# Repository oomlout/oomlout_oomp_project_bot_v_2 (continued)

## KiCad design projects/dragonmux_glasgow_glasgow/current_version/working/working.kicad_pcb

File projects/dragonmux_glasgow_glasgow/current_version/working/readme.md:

# glasgow
 
## summary 
* id: dragonmux_glasgow_glasgow
* user: dragonmux
* name: glasgow
* board: glasgow
* repo: https://github.com/dragonmux/glasgow
* src_file_repo_kicad_pcb: hardware/boards/glasgow.kicad_pcb
* src_file_repo_kicad_pcb_link: https://github.com/dragonmux/glasgow/tree/main/hardware/boards/glasgow.kicad_pcb

* src_file_repo_sch: hardware/boards/glasgow.sch
* src_file_repo_sch_link: https://github.com/dragonmux/glasgow/tree/main/hardware/boards/glasgow.sch
* full details link: https://github.com/oomlout/oomlout_oomp_project_bot_v_2/tree/main/projects/dragonmux_glasgow_glasgow/current_version/working

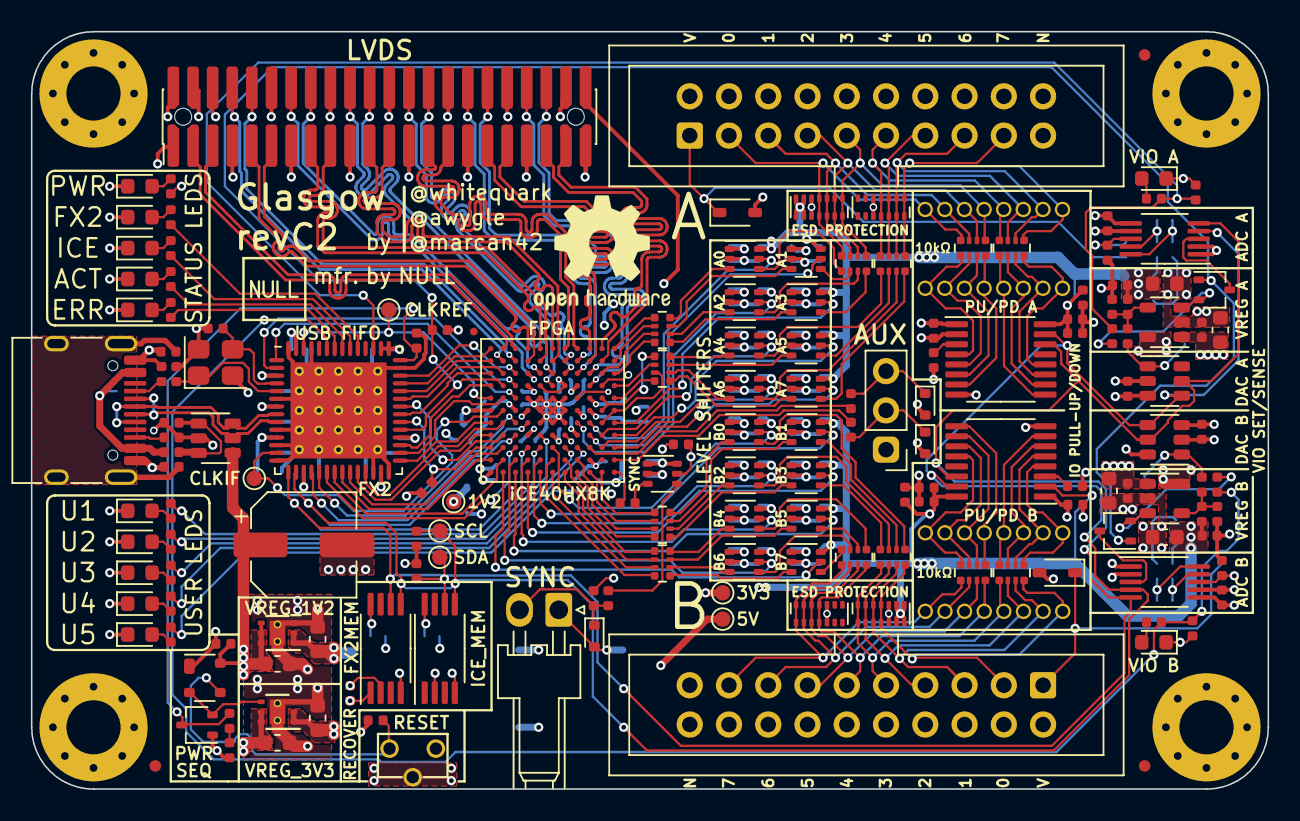
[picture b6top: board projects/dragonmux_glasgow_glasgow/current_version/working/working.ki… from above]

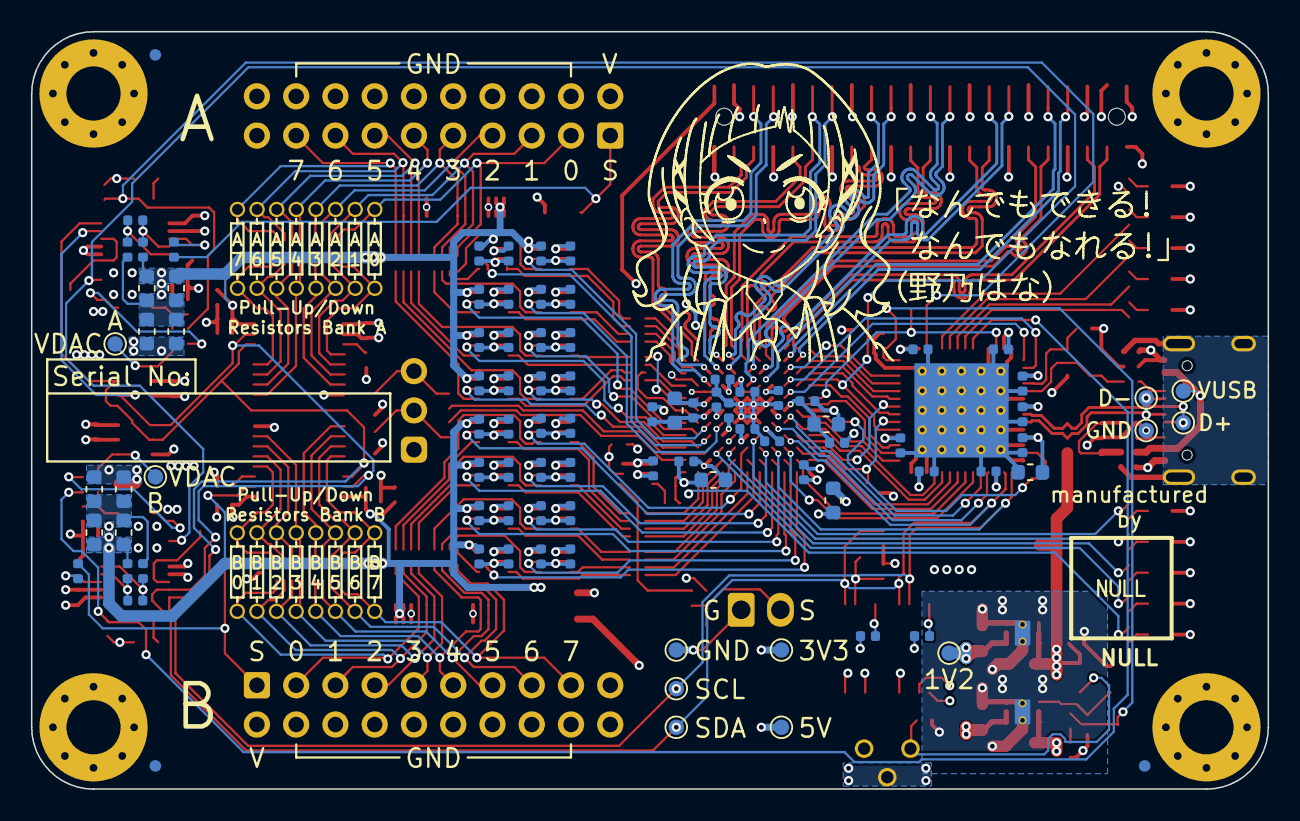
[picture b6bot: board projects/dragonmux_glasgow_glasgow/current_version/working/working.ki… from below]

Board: 4 copper layers, 80.0 x 49.0 mm, 264 parts (93 on the bottom side), 226 nets.

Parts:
C1, C14, C19, C26, C27, C28, C31, C53, C76, C80, C82, C83, C86: 4u7; C_0603_1608Metric
C2, C3, C4, C5, C6, C7, C8, C9, C10, C13, C15, C16, C17, C18, C20, C21, C22, C23, C24, C25, C29, C30, C32, C33, C34, C35, C36, C37, C38, C39, C40, C41, C42, C43, C44, C45, C46, C47, C48, C49, C50, C51, C52, C54, C55, C56, C57, C58, C59, C60, C61, C62, C63, C64, C65, C66, C67, C68, C69, C70, C71, C72, C73, C74, C75, C77, C78, C79, C81, C84, C85, C88, C89: u1; C_0402_1005Metric
C11, C12: 9p; C_0402_1005Metric
C87: 150u; CP_Elec_6.3x5.9
C90, C91: DNP; C_0402_1005Metric_DNP
D1, D2, D3, D14, D15: GRN; LED_0603_1608Metric
D4: YEL; LED_0603_1608Metric
D5: RED; LED_0603_1608Metric
D6, D10: BLU; LED_0603_1608Metric
D7, D9: PNK; LED_0603_1608Metric
D8: WHT; LED_0603_1608Metric
D11, D12, D13: ESD5Z5.0T1G; D_SOD-523
D16, D17: CDSOD323-T36S; D_SOD-323
D18, D19: BAT54CW; SOT-323_SC-70
D20, D21, D22, D23: SP3012-06UTG; UDFN-14_3.5x1.35mm_P0.5mm
D24: BAT54AW; SOT-323_SC-70
FB1: 600R, 0.5A; L_0402_1005Metric
FID1, FID2, FID3, FID4, FID5, FID6: Fiducial_0.75mm_Mask1.5mm
FID8: Fiducial_0.5mm_Dia_1mm_Outer
J1: USB_C_USB2.0; USB_C_Receptacle_HRO_TYPE-C-31-M-12
J2, J3: IDC-Header_2x10_P2.54mm; IDC-Header_2x10_P2.54mm_Vertical
J4: Conn_01x02; Molex_KK-254_1x02_P2.54mm_Horizontal
J5: PinHeader_2x22_P1.27mm; PinHeader_2x22_P1.27mm_Vertical__SMD
J6, J7, J8, J9: Conn_01x08; PinSocket_1x08_P1.27mm_Vertical_DNP
J10: AUX; PinHeader_1x03_P2.54mm_Vertical
MK1, MK2, MK3, MK4: Mounting_Hole_PAD; MountingHole_3.5mm_Pad_Via_CrtYd
NONO_HANA: MECHOKKU; nono_hana_lines
R1, R2, R10, R15, R41, R42, R57, R58: 2k2; R_0402_1005Metric
R3, R4, R5, R9, R17: 100k; R_0402_1005Metric
R6, R8, R50, R51: DNP; R_0603_1608Metric_DNP
R7, R56: 0R33; R_0603_1608Metric
R11, R23: 4k7; R_0402_1005Metric
R12, R13, R14, R46, R47: 20k; R_0402_1005Metric
R16, R18, R19, R20, R22, R26, R36, R37, R44, R55: 10k; R_0402_1005Metric
R21: 6k8; R_0402_1005Metric
R24, R25, R30, R54, R59, R60: 4R7; R_0402_1005Metric
R27, R33: 49k9; R_0402_1005Metric
R28, R34: 59k; R_0402_1005Metric
R29, R35: 24k3; R_0402_1005Metric
R31, R32: 100R; R_0402_1005Metric
R38, R39, R43, R45: 47R; R_0402_1005Metric
R40: DNP; R_0402_1005Metric_DNP
R48, R49: 0R15; R_0603_1608Metric
R52, R53: 5k1; R_0402_1005Metric
RN1, RN2, RN3, RN4, RN7, RN8, RN9, RN10: 33R; R_Array_Convex_4x0402
RN5, RN6, RN11, RN12: 10k; R_Array_Convex_4x0402
SW1: RST; SW_Tactile_SPST_Angled_TC-1109DE
TP1, TP8: 5V; TestPoint_Pad_D1.0mm
TP2, TP17: 1V2; TestPoint_Pad_D1.0mm
TP3, TP7, TP9: 3V3; TestPoint_Pad_D1.0mm
TP4, TP10: SDA; TestPoint_Pad_D1.0mm
TP5, TP11: SCL; TestPoint_Pad_D1.0mm
TP6: CLKREF; TestPoint_Pad_D1.0mm
TP12: GND; TestPoint_Pad_D1.0mm
TP13: VBUS; TestPoint_Pad_D1.0mm
TP14: USBGND; TestPoint_Pad_D1.0mm
TP15: USBDP; TestPoint_Pad_D1.0mm
TP16: USBDM; TestPoint_Pad_D1.0mm
TP18, TP19: VDAC; TestPoint_Pad_D1.0mm
U1: CY7C68013A-56LTX; Cypress_QFN-56-1EP_8x8mm_P0.5mm_EP6.22x6.22mm_ThermalVias
U2: CAT24M01X; TSSOP-8_4.4x3mm_P0.65mm
U3: BL24C256A-SFRC; TSSOP-8_4.4x3mm_P0.65mm
U4, U6, U9, U10, U11, U16, U17, U18, U22, U23, U24, U25, U26, U27, U28, U29, U32: SN74LVC1T45DCKR; SOT-363_SC-70-6
U5, U19: PCA6408APW; TSSOP-16_4.4x5mm_P0.65mm
U7: APX811-40UG-7; SOT-143
U8: TLV75533PDRVR; DFN-6-1EP_2x2mm_P0.65mm_EP1x1.6mm_ThermalVias
U12, U21: INA233; VSSOP-10_3x3mm_P0.5mm
U13, U20: DAC081C081CIMK; SOT-23-6
U14, U31: TPS73101DBV; SOT-23-5
U15: TPD3S014; SOT-23-6
U30: ICE40HX8K-BG121; BGA-121_9.0x9.0mm_Layout11x11_P0.8mm_Ball0.4mm_Pad0.35mm_NS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
U36: TLV73312PQDRVR; DFN-6-1EP_2x2mm_P0.65mm_EP1x1.6mm_ThermalVias
Y1: 24M; Crystal_SMD_3225-4Pin_3.2x2.5mm

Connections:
+1V2: C14.1, C18.1, C24.1, C25.1, C27.1, C77.1, R31.2, R32.2, TP2.1, TP17.1, U30.D4, U30.D8, U30.H4, U30.H8, U36.1, U36.2
+3V3: C1.1, C2.1, C3.1, C4.1, C5.1, C6.1, C7.1, C9.1, C10.1, C15.1, C17.1, C19.1, C20.1, C21.1, C22.1, C23.1, C28.1, C30.1, C32.1, C34.1, C35.1, C36.1, C37.1, C42.1, C43.1, C47.1, C48.1, C55.1, C56.1, C60.1, C61.1, C62.1, C63.1, C68.1, C69.1, C70.1, C71.1, C81.1, C84.1, C85.1, D24.1, J5.2, R1.2, R2.2, R4.1, R12.1, R17.2, R36.2, R37.2, R40.2, R44.2, TP3.1, TP9.1, U1.3, U1.7, U1.11, U1.17, U1.27, U1.32, U1.43, U1.44, U1.55, U2.2, U2.8, U3.1, U3.8, U4.1, U5.1, U6.1, U8.1, U8.2, U9.1, U10.1, U11.1, U12.2, U12.6, U13.2, U16.1, U17.1, U18.1, U19.1, U20.2, U21.6, U22.1, U23.1, U24.1, U25.1, U26.1, U27.1, U28.1, U29.1, U30.C10, U30.D6, U30.F8, U30.H6, U30.L11, U32.1, U32.6
+5V: C16.1, C26.2, C31.1, C45.1, C59.1, C82.1, C86.2, C87.1, TP1.1, TP8.1, U7.4, U8.5, U8.6, U14.1, U15.4, U31.1, U36.4, U36.5, U36.6
/A0: U1.37, U30.K3
/A1: U1.38, U30.L2
/CC1: J1.A5, R53.2
/CC2: J1.B5, R52.2
/CLKIF: TP7.1, U1.13, U30.K6
/CLKREF: TP6.1, U1.54, U30.D5, U30.L5
/D0: U1.18, U30.H7
/D1: U1.19, U30.J7
/D2: U1.20, U30.J9
/D3: U1.21, U30.K10
/D4: U1.22, U30.L10
/D5: U1.23, U30.K9
/D6: U1.24, U30.L8
/D7: U1.25, U30.K7
/ENVA: R18.1, R47.1, R55.2, U1.45
/ENVB: R19.1, R26.2, R46.1, U1.51
/FLAGA: U1.29, U30.L7
/FLAGB: U1.30, U30.K5
/FLAGC: U1.31, U30.L4
/FLAGD: U1.40, U30.J3
/FPGA_DONE: U1.36, U30.K8
/GNDPLL0: C76.2, C78.2, U30.L6
/GNDPLL1: C79.2, C80.2, U30.C5
/IO_Banks/DA0: U4.5, U30.C7
/IO_Banks/DA1: U11.5, U30.C8
/IO_Banks/DA2: U6.5, U30.D7
/IO_Banks/DA3: U16.5, U30.A7
/IO_Banks/DA4: U9.5, U30.B8
/IO_Banks/DA5: U17.5, U30.A8
/IO_Banks/DA6: U10.5, U30.B9
/IO_Banks/DA7: U18.5, U30.A9
/IO_Banks/DB0: U22.5, U30.F9
/IO_Banks/DB1: U26.5, U30.G11
/IO_Banks/DB2: U23.5, U30.G10
/IO_Banks/DB3: U27.5, U30.H11
/IO_Banks/DB4: U24.5, U30.H10
/IO_Banks/DB5: U28.5, U30.J11
/IO_Banks/DB6: U25.5, U30.J10
/IO_Banks/DB7: U29.5, U30.K11
/IO_Banks/IO_Buffer_A/ISNS_H: R8.2, R30.1, R49.1, R51.1, R56.2
/IO_Banks/IO_Buffer_A/P0: J9.1, RN11.5, U19.4
/IO_Banks/IO_Buffer_A/P1: J9.2, RN11.6, U19.5
/IO_Banks/IO_Buffer_A/P2: J9.3, RN11.7, U19.6
/IO_Banks/IO_Buffer_A/P3: J9.4, RN11.8, U19.7
/IO_Banks/IO_Buffer_A/P4: J9.5, RN12.5, U19.9
/IO_Banks/IO_Buffer_A/P5: J9.6, RN12.6, U19.10
/IO_Banks/IO_Buffer_A/P6: J9.7, RN12.7, U19.11
/IO_Banks/IO_Buffer_A/P7: J9.8, RN12.8, U19.12
/IO_Banks/IO_Buffer_A/VDAC: R33.1, TP19.1, U20.1
/IO_Banks/IO_Buffer_A/VFB: R33.2, R34.1, R35.2, U31.4
/IO_Banks/IO_Buffer_A/VIO_EN: D19.2, R55.1, U31.3
/IO_Banks/IO_Buffer_A/VSENSE: D17.1, J2.1, R60.2
/IO_Banks/IO_Buffer_A/X0: RN7.8, U4.3
/IO_Banks/IO_Buffer_A/Y0: RN9.1, U4.4
/IO_Banks/IO_Buffer_A/Y1: RN9.2, U11.4
/IO_Banks/IO_Buffer_A/Y2: RN9.3, U6.4
/IO_Banks/IO_Buffer_A/Y3: RN9.4, U16.4
/IO_Banks/IO_Buffer_A/Y4: RN10.1, U9.4
/IO_Banks/IO_Buffer_A/Y5: RN10.2, U17.4
/IO_Banks/IO_Buffer_A/Y6: RN10.3, U10.4
/IO_Banks/IO_Buffer_A/Y7: RN10.4, U18.4
/IO_Banks/IO_Buffer_A/Z0: D22.4, D22.11, J2.3, J8.1, RN9.8, RN11.4
/IO_Banks/IO_Buffer_A/Z1: D22.3, D22.12, J2.5, J8.2, RN9.7, RN11.3
/IO_Banks/IO_Buffer_A/Z2: D22.2, D22.13, J2.7, J8.3, RN9.6, RN11.2
/IO_Banks/IO_Buffer_A/Z3: D22.1, D22.14, J2.9, J8.4, RN9.5, RN11.1
/IO_Banks/IO_Buffer_A/Z4: D23.4, D23.11, J2.11, J8.5, RN10.8, RN12.4
/IO_Banks/IO_Buffer_A/Z5: D23.3, D23.12, J2.13, J8.6, RN10.7, RN12.3
/IO_Banks/IO_Buffer_A/Z6: D23.2, D23.13, J2.15, J8.7, RN10.6, RN12.2
/IO_Banks/IO_Buffer_A/Z7: D23.1, D23.14, J2.17, J8.8, RN10.5, RN12.1
/IO_Banks/IO_Buffer_B/ISNS_H: R6.2, R7.2, R24.1, R48.1, R50.1
/IO_Banks/IO_Buffer_B/P0: J7.1, RN5.5, U5.4
/IO_Banks/IO_Buffer_B/P1: J7.2, RN5.6, U5.5
/IO_Banks/IO_Buffer_B/P2: J7.3, RN5.7, U5.6
/IO_Banks/IO_Buffer_B/P3: J7.4, RN5.8, U5.7
/IO_Banks/IO_Buffer_B/P4: J7.5, RN6.5, U5.9
/IO_Banks/IO_Buffer_B/P5: J7.6, RN6.6, U5.10
/IO_Banks/IO_Buffer_B/P6: J7.7, RN6.7, U5.11
/IO_Banks/IO_Buffer_B/P7: J7.8, RN6.8, U5.12
/IO_Banks/IO_Buffer_B/VDAC: R27.1, TP18.1, U13.1
/IO_Banks/IO_Buffer_B/VFB: R27.2, R28.1, R29.2, U14.4
/IO_Banks/IO_Buffer_B/VIO_EN: D18.2, R26.1, U14.3
/IO_Banks/IO_Buffer_B/VSENSE: D16.1, J3.1, R59.2
/IO_Banks/IO_Buffer_B/X0: RN1.8, U22.3
/IO_Banks/IO_Buffer_B/Y0: RN3.1, U22.4
/IO_Banks/IO_Buffer_B/Y1: RN3.2, U26.4
/IO_Banks/IO_Buffer_B/Y2: RN3.3, U23.4
/IO_Banks/IO_Buffer_B/Y3: RN3.4, U27.4
/IO_Banks/IO_Buffer_B/Y4: RN4.1, U24.4
/IO_Banks/IO_Buffer_B/Y5: RN4.2, U28.4
/IO_Banks/IO_Buffer_B/Y6: RN4.3, U25.4
/IO_Banks/IO_Buffer_B/Y7: RN4.4, U29.4
/IO_Banks/IO_Buffer_B/Z0: D20.4, D20.11, J3.3, J6.1, RN3.8, RN5.4
/IO_Banks/IO_Buffer_B/Z1: D20.3, D20.12, J3.5, J6.2, RN3.7, RN5.3
/IO_Banks/IO_Buffer_B/Z2: D20.2, D20.13, J3.7, J6.3, RN3.6, RN5.2
/IO_Banks/IO_Buffer_B/Z3: D20.1, D20.14, J3.9, J6.4, RN3.5, RN5.1
/IO_Banks/IO_Buffer_B/Z4: D21.4, D21.11, J3.11, J6.5, RN4.8, RN6.4
/IO_Banks/IO_Buffer_B/Z5: D21.3, D21.12, J3.13, J6.6, RN4.7, RN6.3
/IO_Banks/IO_Buffer_B/Z6: D21.2, D21.13, J3.15, J6.7, RN4.6, RN6.2
/IO_Banks/IO_Buffer_B/Z7: D21.1, D21.14, J3.17, J6.8, RN4.5, RN6.1
/IO_Banks/QA0: RN7.1, U30.A1
/IO_Banks/QA1: RN7.2, U30.A2
/IO_Banks/QA2: RN7.3, U30.B3
/IO_Banks/QA3: RN7.4, U30.A3
/IO_Banks/QA4: RN8.1, U30.B5, U30.B6
/IO_Banks/QA5: RN8.2, U30.A4
/IO_Banks/QA6: RN8.3, U30.A6, U30.B7
/IO_Banks/QA7: RN8.4, U30.A5
/IO_Banks/QB0: RN1.1, U30.B11
/IO_Banks/QB1: RN1.2, U30.C11
/IO_Banks/QB2: RN1.3, U30.D10
/IO_Banks/QB3: RN1.4, U30.D11
/IO_Banks/QB4: RN2.1, U30.E10
/IO_Banks/QB5: RN2.2, U30.E11
/IO_Banks/QB6: RN2.3, U30.F11
/IO_Banks/QB7: RN2.4, U30.F10
/IO_Banks/U1: R11.1, U30.G9
/IO_Banks/U2: R20.1, U30.G8
/IO_Banks/U3: R21.1, U30.E9
/IO_Banks/U4: R22.1, U30.D9
/IO_Banks/U5: R23.1, U30.E8
/IO_Banks/VIOA: C38.1, C39.1, C40.1, C41.1, C49.1, C50.1, C51.1, C52.1, C54.1, C57.1, C83.1, D22.6, D22.7, D22.8, D22.9, J2.2, R34.2, R42.2, R49.2, R51.2, R54.1, R58.2, U4.6, U6.6, U9.6, U10.6, U11.6, U16.6, U17.6, U18.6, U19.16
/IO_Banks/VIOB: C29.1, C46.1, C53.1, C64.1, C65.1, C66.1, C67.1, C72.1, C73.1, C74.1, C75.1, D20.6, D20.7, D20.8, D20.9, J3.2, R25.1, R28.2, R41.2, R48.2, R50.2, R57.2, U5.2, U5.16, U22.6, U23.6, U24.6, U25.6, U26.6, U27.6, U28.6, U29.6
/IO_Banks/VIO_AUX: C33.1, J5.44, U30.E4, U30.G4
/IO_Banks/Z0_N: J5.41, U30.B2
/IO_Banks/Z0_P: J5.39, U30.B1
/IO_Banks/Z1_N: J5.38, U30.C3
/IO_Banks/Z1_P: J5.40, U30.C4
/IO_Banks/Z2_N: J5.33, U30.C1
/IO_Banks/Z2_P: J5.35, U30.C2
/IO_Banks/Z3_N: J5.29, U30.D1
/IO_Banks/Z3_P: J5.27, U30.E1
/IO_Banks/Z4_N: J5.34, U30.D3
/IO_Banks/Z4_P: J5.32, U30.D2
/IO_Banks/Z5_N: J5.26, U30.E3
/IO_Banks/Z5_P: J5.28, U30.E2
/IO_Banks/Z6_N: J5.23, U30.F2
/IO_Banks/Z6_P: J5.21, U30.F1
/IO_Banks/Z7_N: J5.20, U30.F3
/IO_Banks/Z7_P: J5.22, U30.F4
/IO_Banks/Z8_N: J5.17, U30.G2
/IO_Banks/Z8_P: J5.15, U30.G1
/IO_Banks/Z9_N: J5.14, U30.H3
/IO_Banks/Z9_P: J5.16, U30.G3
/IO_Banks/Z10_N: J5.11, U30.H2
/IO_Banks/Z10_P: J5.9, U30.H1
/IO_Banks/Z11_N: J5.3, U30.K1
/IO_Banks/Z11_P: J5.5, U30.J1
/IO_Banks/Z12_N: J5.10, U30.J2
/IO_Banks/Z12_P: J5.8, U30.K2
/IO_Banks/~SYNC: D11.1, J4.2, R38.1, R44.1
/LED_ACT: R15.1, U1.49
/LED_CY: R13.1, U1.47
/LED_ERR: R16.1, U1.50
/LED_FPGA: R14.1, U1.48
/OE: U1.35, U30.L3
/PKTEND: U1.39, U30.L1
/RD: U1.1, U30.J5
/SCL: R2.1, TP5.1, TP11.1, U1.15, U2.6, U3.6, U5.14, U12.5, U13.5, U19.14, U20.5, U21.5, U30.H9
/SDA: R1.1, TP4.1, TP10.1, U1.16, U2.5, U3.5, U5.15, U12.4, U13.4, U19.15, U20.4, U21.4, U30.J8
/SHLD: C13.1, J1.S1, R3.1
/USB_N: J1.A7, J1.B7, TP16.1, U1.9, U15.5
/USB_P: J1.A6, J1.B6, TP15.1, U1.8, U15.6
/VCCPLL0: C76.1, C78.1, R31.1, U30.J6
/VCCPLL1: C79.1, C80.1, R32.1, U30.C6
/VUSB: C8.1, FB1.2, U15.1, U15.3
/WR: U1.2, U30.J4
/XTALIN: C12.1, U1.5, Y1.1
/XTALOUT: C11.1, U1.4, Y1.3
/xVBUS: FB1.1, J1.A4, J1.A9, J1.B4, J1.B9, TP13.1
/~ALERT: D18.1, D19.1, R17.1, U1.33, U30.K4
/~CY_RESET: C88.1, D24.3, R5.2, U1.42
/~FPGA_RESET: R9.2, U1.34, U30.L9
/~MR: C89.1, SW1.2, U7.3
GND: C1.2, C2.2, C3.2, C4.2, C5.2, C6.2, C7.2, C8.2, C9.2, C10.2, C11.2, C12.2, C13.2, C14.2, C15.2, C16.2, C17.2, C18.2, C19.2, C20.2, C21.2, C22.2, C23.2, C24.2, C25.2, C26.1, C27.2, C28.2, C29.2, C30.2, C31.2, C32.2, C33.2, C34.2, C35.2, C36.2, C37.2, C38.2, C39.2, C40.2, C41.2, C42.2, C43.2, C45.2, C46.2, C47.2, C48.2, C49.2, C50.2, C51.2, C52.2, C53.2, C54.2, C55.2, C56.2, C57.2, C59.2, C60.2, C61.2, C62.2, C63.2, C64.2, C65.2, C66.2, C67.2, C68.2, C69.2, C70.2, C71.2, C72.2, C73.2, C74.2, C75.2, C77.2, C81.2, C82.2, C83.2, C84.2, C85.2, C86.1, C87.2, C88.2, C89.2, C90.1, C91.1, D1.1, D2.1, D3.1, D4.1, D5.1, D6.1, D7.1, D8.1, D9.1, D10.1, D11.2, D12.2, D13.2, D14.1, D15.1, D16.2, D17.2, D20.5, D20.10, D21.5, D21.10, D22.5, D22.10, D23.5, D23.10, J1.A1, J1.A12, J1.B1, J1.B12, J2.4, J2.6, J2.8, J2.10, J2.12, J2.14, J2.16, J2.18, J3.4, J3.6, J3.8, J3.10, J3.12, J3.14, J3.16, J3.18, J4.1, J5.1, J5.4, J5.6, J5.7, J5.12, J5.13, J5.18, J5.19, J5.24, J5.25, J5.30, J5.31, J5.36, J5.37, J5.42, J5.43, J10.1, MK1.1, MK2.1, MK3.1, MK4.1, R3.2, R9.1, R10.2, R18.2, R19.2, R29.1, R35.1, R41.1, R42.1, R52.1, R53.1, R57.1, R58.1, SW1.1, TP12.1, TP14.1, U1.6, U1.10, U1.12, U1.14, U1.26, U1.28, U1.41, U1.53, U1.56, U1.57, U2.4, U3.4, U4.2, U5.8, U6.2, U7.1, U8.3, U8.7, U9.2, U10.2, U11.2, U12.1, U12.7, U13.3, U13.6, U14.2, U15.2, U16.2, U17.2, U18.2, U19.2, U19.8, U20.3, U21.1, U21.2, U21.7, U22.2, U23.2, U24.2, U25.2, U26.2, U27.2, U28.2, U29.2, U30.E5, U30.E6, U30.E7, U30.F5, U30.F6, U30.F7, U30.G5, U30.G6, U30.G7, U30.H5, U31.2, U32.2, U36.3, U36.7, Y1.2, Y1.4
unnamed: C44.1, R25.2, U12.9
unnamed: C44.2, R24.2, U12.10
unnamed: C58.1, R54.2, U21.9
unnamed: C58.2, R30.2, U21.10
unnamed: C90.2, R59.1, U12.8
unnamed: C91.2, R60.1, U21.8
unnamed: D1.2, R12.2
unnamed: D2.2, R13.2
unnamed: D3.2, R14.2
unnamed: D4.2, R15.2
unnamed: D5.2, R16.2
unnamed: D6.2, R11.2
unnamed: D7.2, R20.2
unnamed: D8.2, R21.2
unnamed: D9.2, R22.2
unnamed: D10.2, R23.2
unnamed: D12.1, J10.2, R39.1
unnamed: D13.1, J10.3, R43.1
unnamed: D14.2, R46.2
unnamed: D15.2, R47.2
unnamed: D18.3, U12.3
unnamed: D19.3, U21.3
unnamed: D24.2, U7.2, U8.4
unnamed: R4.2, R5.1
unnamed: R6.1, R7.1, U14.5
unnamed: R10.1, U30.B4, U32.5
unnamed: R36.1, U5.3
unnamed: R37.1, U19.3
unnamed: R38.2, U32.4
unnamed: R39.2, U30.A10
unnamed: R40.1, U3.2
unnamed: R43.2, U30.C9
unnamed: R45.1, U32.3
unnamed: R45.2, U30.A11
unnamed: R8.1, R56.1, U31.5
unnamed: RN1.5, U27.3
unnamed: RN1.6, U23.3
unnamed: RN1.7, U26.3
unnamed: RN2.5, U29.3
unnamed: RN2.6, U25.3
unnamed: RN2.7, U28.3
unnamed: RN2.8, U24.3
unnamed: RN7.5, U16.3
unnamed: RN7.6, U6.3
unnamed: RN7.7, U11.3
unnamed: RN8.5, U18.3
unnamed: RN8.6, U10.3
unnamed: RN8.7, U17.3
unnamed: RN8.8, U9.3

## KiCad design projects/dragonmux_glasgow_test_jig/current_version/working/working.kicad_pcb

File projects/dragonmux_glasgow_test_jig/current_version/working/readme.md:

# glasgow
 
## summary 
* id: dragonmux_glasgow_test_jig
* user: dragonmux
* name: glasgow
* board: test_jig
* repo: https://github.com/dragonmux/glasgow
* src_file_repo_kicad_pcb: hardware/boards/test-jig/test-jig.kicad_pcb
* src_file_repo_kicad_pcb_link: https://github.com/dragonmux/glasgow/tree/main/hardware/boards/test-jig/test-jig.kicad_pcb

* src_file_repo_sch: hardware/boards/glasgow.sch
* src_file_repo_sch_link: https://github.com/dragonmux/glasgow/tree/main/hardware/boards/glasgow.sch
* full details link: https://github.com/oomlout/oomlout_oomp_project_bot_v_2/tree/main/projects/dragonmux_glasgow_test_jig/current_version/working

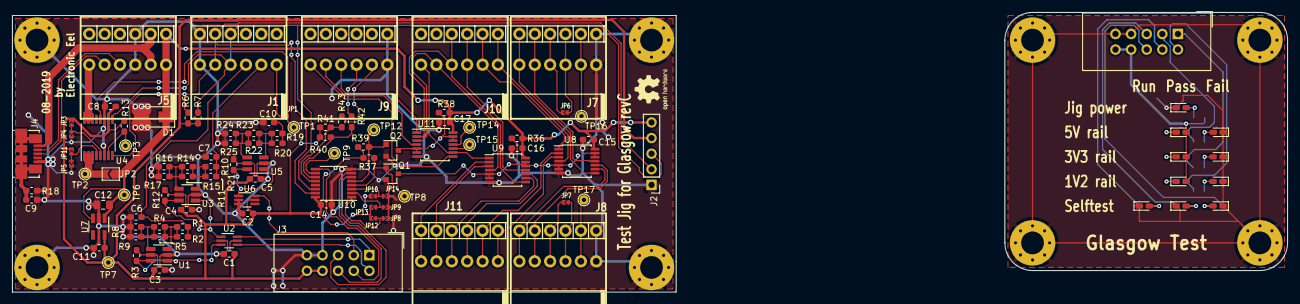
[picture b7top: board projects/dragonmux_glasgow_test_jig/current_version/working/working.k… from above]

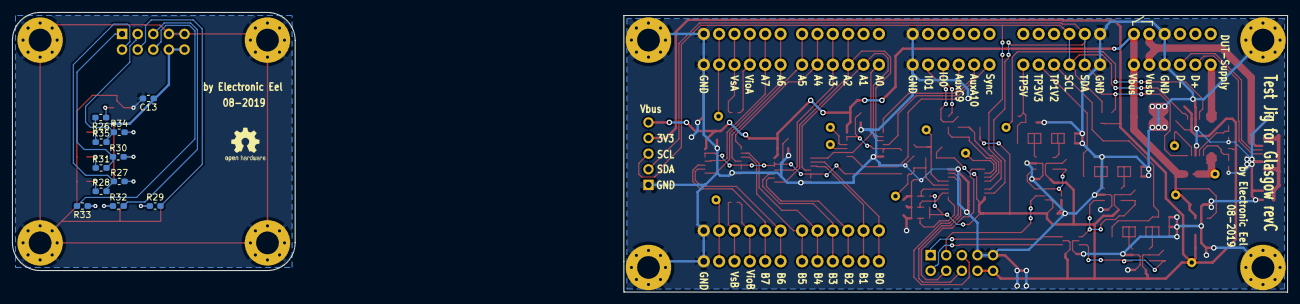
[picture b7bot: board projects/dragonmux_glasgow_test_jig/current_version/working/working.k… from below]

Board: 2 copper layers, 207.5 x 45.5 mm, 129 parts (11 on the bottom side), 90 nets.

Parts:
C1, C2, C3, C4, C5, C6, C7, C8, C9, C10, C13, C14, C15, C16, C17: 100nF; C_0603_1608Metric_Pad1.05x0.95mm_HandSolder
C11: 1µF; C_0603_1608Metric_Pad1.05x0.95mm_HandSolder
C12: 4.7µF; C_0805_2012Metric_Pad1.15x1.40mm_HandSolder
D1: SMAJ5A; D_SMA
D2, D3, D6, D8, D10: green; LED_0603_1608Metric_Castellated
D4, D7, D9, D11: red; LED_0603_1608Metric_Castellated
D5: yellow; LED_0603_1608Metric_Castellated
H1, H2, H3, H4, H5, H6, H7, H8: MountingHole_Pad; MountingHole_3.7mm_Pad_Via
J1, J5, J7, J8, J9, J10, J11: AST04106; TerminalBlock_MetzConnect_AST04106_1x06_Lever_Clamp_45Degree
J2: DNP; PinHeader_1x05_P2.54mm_Vertical
J3, J6: Conn_02x05_Odd_Even; IDC-Header_2x05_P2.54mm_Vertical
J4: USB_B_Micro; USB_Micro-B_Molex_47346-0001
JP1, JP4, JP5, JP6, JP7, JP8, JP9, JP10: SolderJumper_2_Bridged; Solderbridge-small-2pad
JP2: SolderJumper_2_Bridged; SolderJumper-2_P1.3mm_Open_TrianglePad1.0x1.5mm
JP3, JP11, JP12, JP13, JP14: SolderJumper_2_Open; Solderbridge-small-2pad
Q1, Q2: BSS138; SOT-23
R1: 5M1; R_0603_1608Metric_Pad1.05x0.95mm_HandSolder
R2: 68k; R_0603_1608Metric_Pad1.05x0.95mm_HandSolder
R3, R12, R13, R21: 4k7; R_0603_1608Metric_Pad1.05x0.95mm_HandSolder
R4, R8, R16, R22, R24, R40, R41, R42, R43: DNP; R_0603_1608Metric_Pad1.05x0.95mm_HandSolder
R5: 910R; R_0603_1608Metric_Pad1.05x0.95mm_HandSolder
R6, R7: 22k; R_0603_1608Metric_Pad1.05x0.95mm_HandSolder
R9: 33k; R_0603_1608Metric_Pad1.05x0.95mm_HandSolder
R10: 91k; R_0603_1608Metric_Pad1.05x0.95mm_HandSolder
R11: 3M6; R_0603_1608Metric_Pad1.05x0.95mm_HandSolder
R14: 1k; R_0603_1608Metric_Pad1.05x0.95mm_HandSolder
R15: 470R; R_0603_1608Metric_Pad1.05x0.95mm_HandSolder
R17: 12k; R_0603_1608Metric_Pad1.05x0.95mm_HandSolder
R18: 1M; R_0603_1608Metric_Pad1.05x0.95mm_HandSolder
R19: 510k; R_0603_1608Metric_Pad1.05x0.95mm_HandSolder
R20: 110k; R_0603_1608Metric_Pad1.05x0.95mm_HandSolder
R23: 680; R_0603_1608Metric_Pad1.05x0.95mm_HandSolder
R25: 7k5; R_0603_1608Metric_Pad1.05x0.95mm_HandSolder
R26, R27, R28, R29, R30, R31, R32, R33, R34, R35, R36, R38: 2k2; R_0603_1608Metric_Pad1.05x0.95mm_HandSolder
R37, R39: 100K; R_0603_1608Metric_Pad1.05x0.95mm_HandSolder
TP1, TP2, TP3, TP6, TP7, TP8, TP9, TP12, TP14, TP15, TP16, TP17: TestPoint; TestPoint_THTPad_D1.5mm_Drill0.7mm
U1, U3, U5: TPS3700; SOT-23-6_Handsoldering
U2, U6: 74LVC2G14; SOT-363_SC-70-6_Handsoldering
U4: INA260; TSSOP-16_4.4x5mm_P0.65mm
U7: AP2127K-3.3; SOT-23-5_HandSoldering
U8, U9, U11: 74HC4066; TSSOP-14_4.4x5mm_P0.65mm
U10: TCA9534; TSSOP-16_4.4x5mm_P0.65mm

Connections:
+3.3VA: C13.1, D3.2, D6.2, D10.2, J6.8, J6.10, R26.2
+3V3: C1.1, C2.1, C3.1, C4.1, C5.1, C8.1, C11.1, C14.1, J2.4, J3.8, J3.10, JP3.2, JP10.2, JP11.2, JP12.2, JP13.2, R3.1, R6.1, R7.1, R12.1, R13.1, R21.1, R37.1, R39.1, R40.2, R41.2, TP7.1, U1.5, U2.5, U3.5, U4.10, U5.5, U6.5, U7.5, U10.16
/DUT_Supply: J5.6, U4.14, U4.15, U4.16
/LED_1V2: J3.2, U2.4
/LED_3V3: J3.1, U2.6
/LED_5V: J3.3, U6.6
/LED_FAIL: J3.6, U10.7
/LED_PASS: J3.5, U10.6
/LED_RUN: J3.4, U10.9
/SCL: J1.4, J2.3, R7.2, U4.9, U10.14
/SDA: J1.5, J2.2, R6.2, U4.8, U10.15
/TP_1V2: C6.1, J1.3, R1.1, R2.1
/TP_3V3: C7.1, J1.2, R10.1, R11.1
/TP_5V: C10.1, J1.1, JP1.1, R19.1, R20.1
/led-board/LED_1V2: J6.2, R27.1, R28.2
/led-board/LED_3V3: J6.1, R30.1, R31.2
/led-board/LED_5V: J6.3, R34.1, R35.2
/led-board/LED_FAIL: J6.6, R33.2
/led-board/LED_PASS: J6.5, R32.2
/led-board/LED_RUN: J6.4, R29.2
/port-connection/Aux_conn_ctrl_5V: Q2.3, R38.2, U11.5, U11.6, U11.12, U11.13
/port-connection/JIG_GPIO0: J9.3, R42.2
/port-connection/JIG_GPIO1: J9.2, R43.2
/port-connection/Port_conn_ctrl_5V: Q1.3, R36.2, U8.5, U8.6, U8.12, U8.13, U9.5, U9.6, U9.12, U9.13
/port-connection/TP_A0: J10.6, U9.1, U11.9
/port-connection/TP_A1: J10.5, U9.4, U11.3
/port-connection/TP_A2: J10.4, U9.8, U11.2
/port-connection/TP_A3: J10.3, U9.11
/port-connection/TP_A4: J10.2, U8.1
/port-connection/TP_A5: J10.1, U8.4
/port-connection/TP_A6: J7.6, U8.8
/port-connection/TP_A7: J7.5, U8.11
/port-connection/TP_A_Vio: J7.4, JP6.2
/port-connection/TP_A_Vsns: J7.3, JP6.1
/port-connection/TP_Aux_A10: J9.5, U11.4
/port-connection/TP_Aux_C9: J9.4, U11.1
/port-connection/TP_B0: J11.6, U9.2
/port-connection/TP_B1: J11.5, U9.3
/port-connection/TP_B2: J11.4, U9.9
/port-connection/TP_B3: J11.3, U9.10
/port-connection/TP_B4: J11.2, U8.2
/port-connection/TP_B5: J11.1, U8.3
/port-connection/TP_B6: J8.6, U8.9
/port-connection/TP_B7: J8.5, U8.10
/port-connection/TP_B_Vio: J8.4, JP7.2
/port-connection/TP_B_Vsns: J8.3, JP7.1
/port-connection/TP_Sync: J9.6, U11.8
/port-connection/~Aux_conn_ctrl: Q2.1, R39.2, TP12.1, U10.5
/port-connection/~Port_conn_ctrl: Q1.1, R37.2, TP8.1, U10.4
GND: C1.2, C2.2, C3.2, C4.2, C5.2, C6.2, C7.2, C8.2, C9.2, C10.2, C11.2, C12.2, C14.2, C15.2, C16.2, C17.2, D1.2, H1.1, H2.1, H3.1, H4.1, J1.6, J2.1, J3.7, J3.9, J4.5, J5.3, J7.1, J8.1, J9.1, JP4.2, JP5.2, JP8.2, JP9.2, JP14.2, Q1.2, Q2.2, R8.2, R9.2, R16.2, R17.2, R18.2, R24.2, R25.2, U1.2, U2.2, U3.2, U4.6, U4.11, U5.2, U6.2, U6.3, U7.2, U8.7, U9.7, U10.8, U11.7
GNDA: C13.2, D2.1, D4.1, D5.1, D7.1, D8.1, D9.1, D11.1, H5.1, H6.1, H7.1, H8.1, J6.7, J6.9
unnamed: C9.1, J4.6, R18.1
unnamed: D2.2, R26.1
unnamed: D3.1, R27.2
unnamed: D4.2, R28.1
unnamed: D5.2, R29.1
unnamed: D6.1, R30.2
unnamed: D7.2, R31.1
unnamed: D8.2, R32.1
unnamed: D9.2, R33.1
unnamed: D10.1, R34.2
unnamed: D11.2, R35.1
unnamed: J4.1, J5.2
unnamed: J4.2, J5.4
unnamed: J4.3, J5.5
unnamed: J7.2, TP16.1
unnamed: J8.2, TP17.1
unnamed: JP1.2, TP1.1, U4.12
unnamed: JP2.2, TP2.1, U4.1, U4.2, U4.3
unnamed: JP3.1, JP4.1, U4.5
unnamed: JP10.1, JP14.1, U10.3
unnamed: JP5.1, JP11.1, U4.4
unnamed: JP8.1, JP12.1, U10.1
unnamed: JP9.1, JP13.1, U10.2
unnamed: R1.2, R2.2, R4.1, R5.1, U1.3
unnamed: R3.2, U1.1, U1.6, U2.3
unnamed: R4.2, R5.2, R8.1, R9.1, U1.4
unnamed: R10.2, R11.2, R14.1, R15.1, U3.3
unnamed: R12.2, U2.1, U3.1, U3.6
unnamed: R13.2, TP3.1, U4.7
unnamed: R14.2, R15.2, R16.1, R17.1, U3.4
unnamed: R19.2, R20.2, R22.1, R23.1, U5.3
unnamed: R21.2, U5.1, U5.6, U6.1
unnamed: R22.2, R23.2, R24.1, R25.1, U5.4
unnamed: R40.1, R42.1, U10.11
unnamed: R41.1, R43.1, U10.12
unnamed: TP9.1, U10.10
unnamed: TP14.1, U11.11
unnamed: TP15.1, U11.10
VBUS: C12.1, C15.1, C16.1, C17.1, D1.1, J2.5, J5.1, JP2.1, R36.1, R38.1, TP6.1, U7.1, U7.3, U8.14, U9.14, U11.14

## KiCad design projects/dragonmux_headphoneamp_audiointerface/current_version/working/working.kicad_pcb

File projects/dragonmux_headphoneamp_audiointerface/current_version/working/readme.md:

# headphoneamp
 
## summary 
* id: dragonmux_headphoneamp_audiointerface
* user: dragonmux
* name: headphoneamp
* board: audiointerface
* repo: https://github.com/dragonmux/HeadphoneAmp
* src_file_repo_kicad_pcb: hardware/AudioInterface/AudioInterface.kicad_pcb
* src_file_repo_kicad_pcb_link: https://github.com/dragonmux/HeadphoneAmp/tree/main/hardware/AudioInterface/AudioInterface.kicad_pcb
* src_file_repo_kicad_sch: hardware/AudioInterface/AudioInterface.kicad_sch
* src_file_repo_kicad_sch_link: https://github.com/dragonmux/HeadphoneAmp/tree/main/hardware/AudioInterface/AudioInterface.kicad_sch

* src_file_repo_sch: 
* src_file_repo_sch_link: https://github.com/dragonmux/HeadphoneAmp/tree/main/
* full details link: https://github.com/oomlout/oomlout_oomp_project_bot_v_2/tree/main/projects/dragonmux_headphoneamp_audiointerface/current_version/working

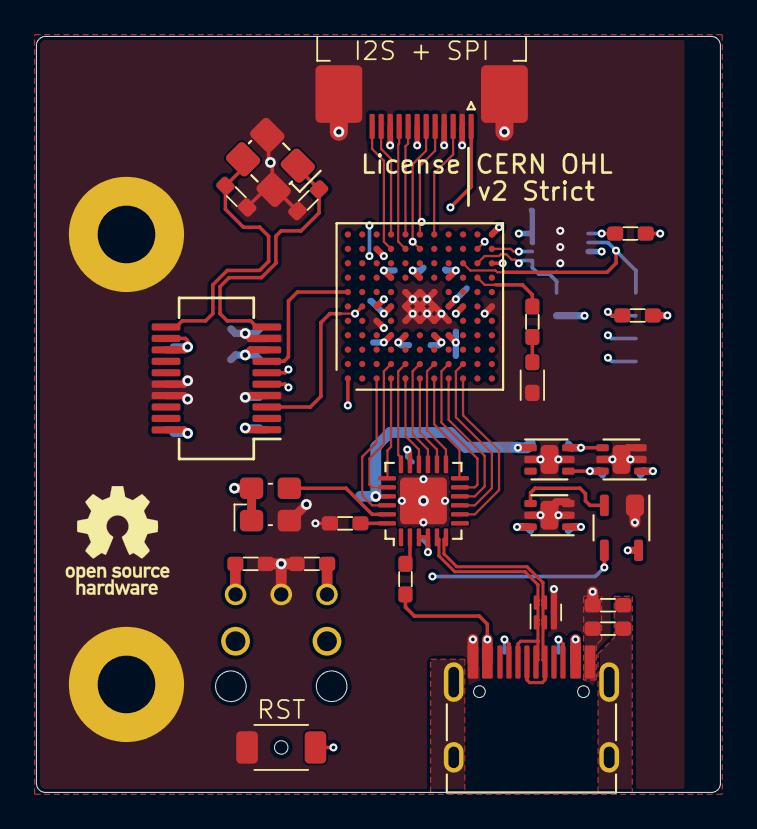
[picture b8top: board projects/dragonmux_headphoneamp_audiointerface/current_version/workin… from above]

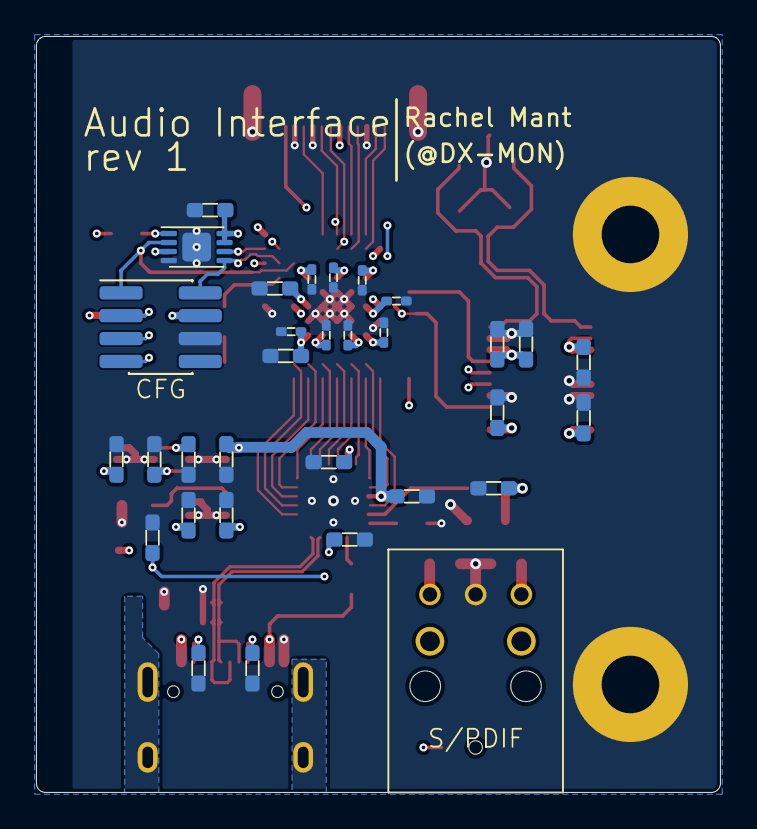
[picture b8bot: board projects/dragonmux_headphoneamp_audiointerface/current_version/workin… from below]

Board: 4 copper layers, 38.0 x 42.0 mm, 60 parts (32 on the bottom side), 47 nets.

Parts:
C1, C4, C6, C8, C9, C10, C11, C12, C20, C21: 0u1; C0603
C2, C3: 15p; C0603
C5: 10u; C0603
C7: 30p; C0603
C13, C14, C15: 1u; C0603
C16, C17, C18, C19, C22, C23, C28: 4u7; C0603
C24, C25, C26, C27, C29, C30, C31, C32: 0u1; C0402
D1: WHITE; LED0603
G1: OSHW-Logo_5.7x6mm_SilkScreen
H1, H2: MountingHole_Pad; MountingHole_3.2mm_M3_Pad
J1: I2S + SPI; 1-17345952-2_1x12-1MP_P0.5mm_Horizontal
J2: USB_C_Receptacle_USB2.0; USB_C_Receptacle_HRO_TYPE-C-31-M-12
J3: S/PDIF; S-PDIF_Receiver
J4: CFG; PinHeader_2x04_P1.27mm_Vertical_SMD
R1: 1M; R0603
R2, R3: 5k1; R0603
R4: 8k06; R0603
R5, R6, R7: 10k; R0603
R8: 6k8; R0603
SW1: RST; B3U-1000P-B
U1: USB3318; QFN-24-1EP_4x4mm_P0.5mm_EP2.6x2.6mm
U2: ICE40HX8K-BG121; BGA-121_9.0x9.0mm_Layout11x11_P0.8mm_Ball0.4mm_Pad0.35mm_NS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
U3: PLL1708; SSOP-20_3.9x8.7mm_P0.635mm
U4: SP3400-02UTG; UDFN-6L
U5: GD25Q40C; UDFN-8-1EP_3x2mm_P0.5mm_EP1.4x1.4mm
U6: TLV75533PDRV; WSON-6-1EP_2x2mm_P0.65mm_EP1x1.6mm
U7: APX811-40UG-7; SOT-143
U8: TLV73312PDRV; WSON-6-1EP_2x2mm_P0.65mm_EP1x1.6mm
U9: LP5910-1.8DRV; WSON-6-1EP_2x2mm_P0.65mm_EP1x1.6mm
X1: 13MHz; SMD2520
Y1: 27MHz; SMD3225

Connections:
+1V2: C19.2, C23.2, C24.2, C25.2, C26.2, C27.2, U2.C6 (VCCPLL1), U2.D4 (VCC), U2.D8 (VCC), U2.H4 (VCC), U2.H8 (VCC), U2.J6 (VCCPLL0), U8.1 (OUT)
+1V8: C14.2, C20.2, U1.21 (VDD18), U9.1 (OUT)
+3V3: C4.2, C5.2, C6.2, C8.2, C9.2, C10.2, C11.2, C12.2, C13.2, C17.2, C18.2, C21.2, C22.2, C28.2, C29.2, C30.2, C31.2, C32.2, J1.7, J3.3 (VCC), J4.4, R5.1, R6.1, U1.3 (VBAT), U1.4 (VDD33), U1.17 (VDDIO), U2.C10 (VPP_2V5), U2.D6 (VCCIO_0), U2.E4 (VCCIO_3), U2.F8 (VCCIO_1), U2.G4 (VCCIO_3), U2.H6 (VCCIO_2), U2.L11 (VCC_SPI), U3.1 (VDD), U3.8 (VCC), U3.12 (CSEL), U3.13 (VDD), U3.20 (VDD), U5.3 (~WP), U5.7 (~HOLD), U5.8 (VCC), U6.1 (OUT), U8.4 (EN), U8.6 (IN), U9.4 (EN), U9.6 (IN), X1.1 (EN), X1.4 (Vdd)
+5V: C16.2, J2.A4 (VBUS), J2.A9 (VBUS), J2.B4 (VBUS), J2.B9 (VBUS), R7.2, U6.6 (IN), U7.4 (VCC)
/ACLK: J1.9, U2.E10 (IOR_141_GBIN2)
/ADAT: J1.11, U2.D11 (IOR_152)
/AR/~L: J1.12, U2.D10 (IOR_154)
/Clock Generation/~SPI_CS: U2.A7 (IOT_192), U3.7 (~CS)
/Power/~PSU_EN: U6.4 (EN), U7.2 (~RST)
/Processing/CFG_CLK: J4.7, U2.L10 (IOB_107_SCK), U5.6 (SCLK)
/Processing/CFG_SPI.CIPO: J1.3, U2.G11 (IOR_129)
/Processing/CFG_SPI.CLK: J1.5, U2.F11 (IOR_140_GBIN3), U3.6 (SCLK)
/Processing/CFG_SPI.COPI: J1.6, U2.F10 (IOR_136), U3.5 (COPI)
/Processing/CIPO: J4.1, U2.J9 (IOB_106_SDI), U5.2 (CIPO)
/Processing/COPI: J4.2, U2.K9 (IOB_105_SDO), U5.5 (COPI)
/Processing/ULPI.CLK: U1.12 (CLKOUT), U2.G1 (IOL_14A_GBIN6)
/Processing/ULPI.D0: U1.16 (DATA0), U2.E1 (IOL_8A)
/Processing/ULPI.D1: U1.15 (DATA1), U2.F2 (IOL_12B)
/Processing/ULPI.D2: U1.14 (DATA2), U2.F1 (IOL_12A)
/Processing/ULPI.D3: U1.13 (DATA3), U2.G2 (IOL_14B)
/Processing/ULPI.D4: U1.11 (DATA4), U2.H2 (IOL_18B)
/Processing/ULPI.D5: U1.10 (DATA5), U2.H1 (IOL_18A)
/Processing/ULPI.D6: U1.9 (DATA6), U2.J2 (IOL_25B)
/Processing/ULPI.D7: U1.8 (DATA7), U2.J1 (IOL_23A)
/Processing/ULPI.DIR: U1.19 (DIR), U2.D1 (IOL_8B)
/Processing/ULPI.NXT: U1.18 (NXT), U2.E2 (IOL_10A)
/Processing/ULPI.STP: U1.20 (STP), U2.D2 (IOL_9A)
/Processing/ULPI.~RST: U1.22 (~RESET), U2.C1 (IOL_5B)
/Processing/~CFG_CS: J4.5, R5.2, U2.K10 (IOB_108_SS), U5.1 (~CS)
/Processing/~CFG_RST: J4.3, R6.2, U2.L9 (~CRESET)
/SYS_CLK: J1.1, U2.B6 (IOT_198_GBIN0), U3.3 (SCKO3)
/S/PDIF: C7.2, J3.1 (Vout), U2.A1 (IOT_225)
/USB/D+: J2.A6 (D+), J2.B6 (D+), U1.6 (DP), U4.2 (IO2), U4.5 (NC)
/USB/D-: J2.A7 (D-), J2.B7 (D-), U1.5 (DM), U4.1 (IO1), U4.6 (NC)
/USB/SHIELD: C1.1, J2.S1 (SHIELD), R1.1
/~DAC_CS: J1.8, U2.E11 (IOR_148)
DGND: C1.2, C2.1, C3.1, C4.1, C5.1, C6.1, C7.1, C8.1, C9.1, C10.1, C11.1, C12.1, C13.1, C14.1, C15.2, C16.1, C17.1, C18.1, C19.1, C20.1, C21.1, C22.1, C23.1, C24.1, C25.1, C26.1, C27.1, C28.1, C29.1, C30.1, C31.1, C32.1, D1.1 (K), H1.1, H2.1, J1.2, J1.4, J1.10, J1.MP (MountPin), J2.A1 (GND), J2.A12 (GND), J2.B1 (GND), J2.B12 (GND), J3.2 (GND), J4.6, R1.2, R2.2, R3.2, R4.1, SW1.2, U1.25 (GND), U2.C5 (GNDPLL1), U2.E5 (GND), U2.E6 (GND), U2.E7 (GND), U2.F5 (GND), U2.F6 (GND), U2.F7 (GND), U2.G5 (GND), U2.G6 (GND), U2.G7 (GND), U2.H5 (GND), U2.L6 (GNDPLL0), U3.4 (DGND), U3.9 (AGND), U3.16 (DGND), U3.17 (DGND), U4.3 (GND), U4.4 (GND), U5.4 (GND), U5.9 (GND), U6.2 (NC), U6.3 (GND), U6.5 (NC), U6.7 (GND), U7.1 (GND), U8.2 (NC), U8.3 (GND), U8.5 (NC), U8.7 (GND), U9.2 (NC), U9.5 (GND), U9.7 (EP), X1.2 (GND), Y1.2, Y1.4
unnamed: C2.2, U3.11 (XT2), Y1.3
unnamed: C3.2, U3.10 (XT1), Y1.1
unnamed: C15.1, SW1.1, U7.3 (~MR)
unnamed: D1.2 (A), R8.2
unnamed: J2.A5 (CC1), R2.1
unnamed: J2.B5 (CC2), R3.1
unnamed: R4.2, U1.24 (RBIAS)
unnamed: R7.1, U1.2 (VBUS)
unnamed: R8.1, U2.K8 (CDONE)
unnamed: U1.23 (REFCLK), X1.3 (OUT)
